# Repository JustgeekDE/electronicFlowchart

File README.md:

# electronicFlowchart
Electronic Flowchart - Physical flowchart components to create simple programs

Electronic Flowchart aims to make program flow charts more tangible. By connecting physical control nodes with actual wires and showing which node is active at any given time, the program flow is shown expölicitly while it's happening

## ToDos:
- Code

### Nodes
- Register node
- Conditional node
- indirect register selector (mux / load) node

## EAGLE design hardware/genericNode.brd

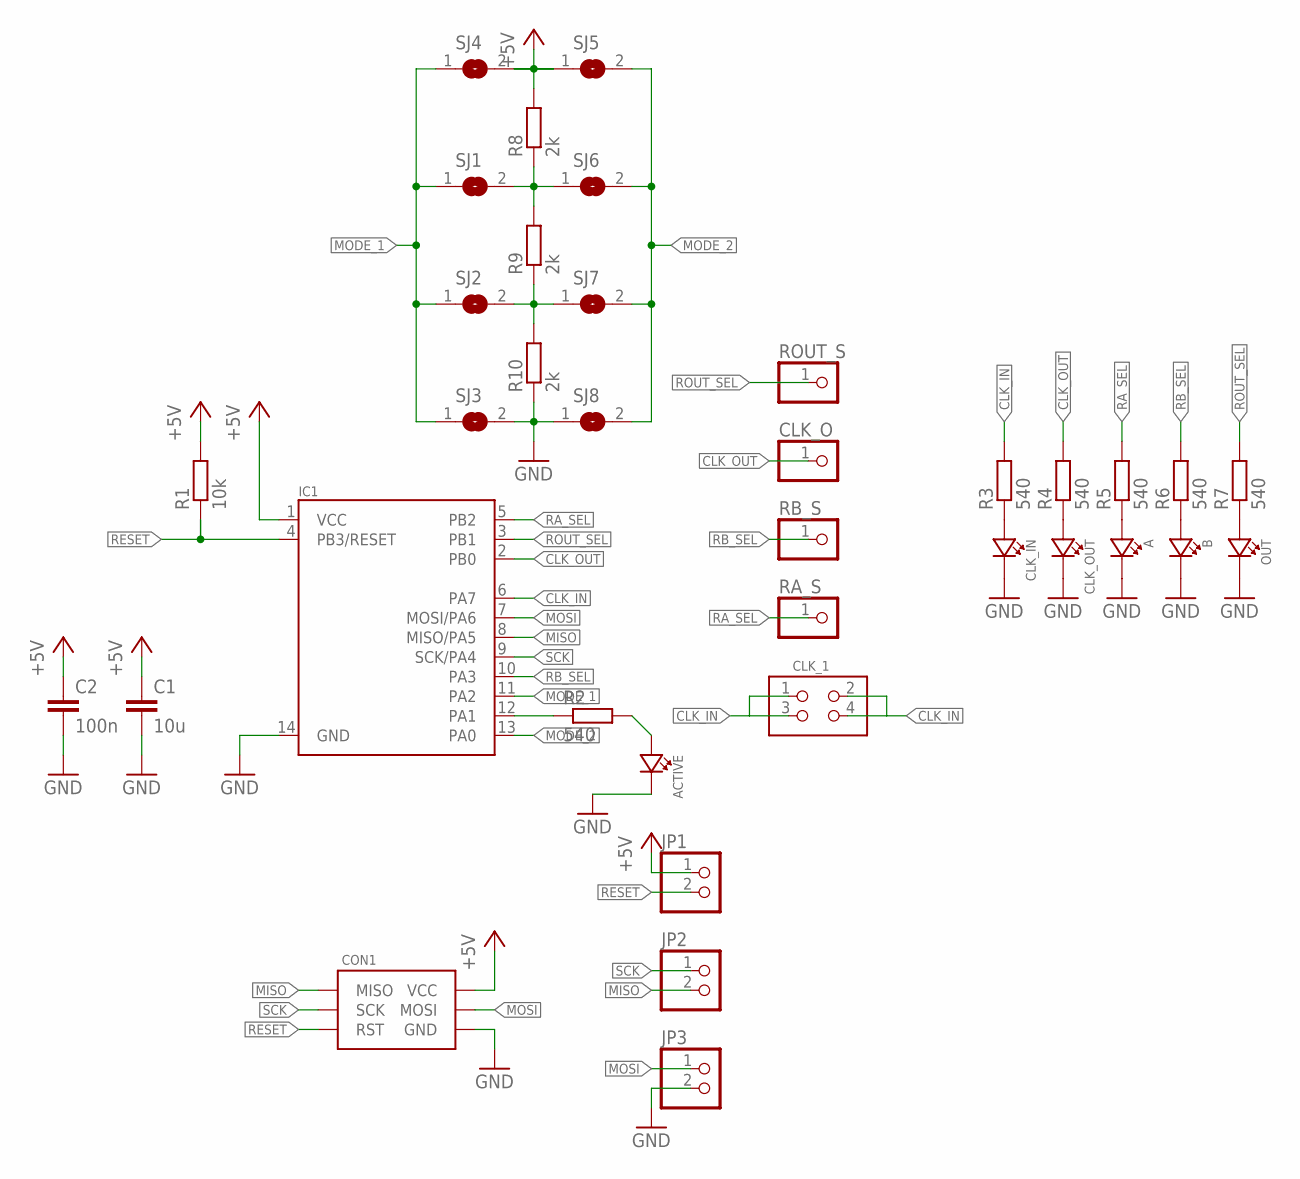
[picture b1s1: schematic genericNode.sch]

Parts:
A: LED0805; CHIPLED_0805
ACTIVE: LED0805; CHIPLED_0805
B: LED0805; CHIPLED_0805
C1: 10u; C0805
C2: 100n; C0603
CLK_1: GENERIC-2X2-EDGE; PINHEADER-100MIL-2X2-EDGE
CLK_IN: LED0805; CHIPLED_0805
CLK_O: PINHD-1X1; 1X01
CLK_OUT: LED0805; CHIPLED_0805
CON1: ISP-6_PIN-POGO; POGO-1.27-6_PIN-MADWORM
IC1: AVR-ATTINY24/44/84-SOIC14; SOIC14
JP1, JP2, JP3: PINHD-1X2; 1X02
OUT: LED0805; CHIPLED_0805
R1: 10k; R0603
R2, R3, R4, R5, R6, R7: 540; R0603
R8, R9, R10: 2k; R0603
RA_S: PINHD-1X1; 1X01
RB_S: PINHD-1X1; 1X01
ROUT_S: PINHD-1X1; 1X01
SJ1, SJ2, SJ3, SJ4, SJ5, SJ6, SJ7, SJ8: SJ

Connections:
+5V: C1.1, C2.1, CON1.P$2 (VCC), IC1.1 (VCC), JP1.1, R1.2, R8.2, SJ4.2, SJ5.1
CLK_IN: CLK_1.1, CLK_1.2, CLK_1.3, CLK_1.4, IC1.6 (PA7), R3.2
CLK_OUT: CLK_O.1, IC1.2 (PB0), R4.2
GND: A.C, ACTIVE.C, B.C, C1.2, C2.2, CLK_IN.C, CLK_OUT.C, CON1.P$6 (GND), IC1.14 (GND), JP3.2, OUT.C, R10.1, SJ3.2, SJ8.1
MISO: CON1.P$1 (MISO), IC1.8 (MISO/PA5), JP2.2
MODE_1: IC1.11 (PA2), SJ1.1, SJ2.1, SJ3.1, SJ4.1
MODE_2: IC1.13 (PA0), SJ5.2, SJ6.2, SJ7.2, SJ8.2
MOSI: CON1.P$4 (MOSI), IC1.7 (MOSI/PA6), JP3.1
unnamed: ACTIVE.A, R2.2
unnamed: IC1.12 (PA1), R2.1
unnamed: CLK_IN.A, R3.1
unnamed: CLK_OUT.A, R4.1
unnamed: A.A, R5.1
unnamed: B.A, R6.1
unnamed: R9.1, R10.2, SJ2.2, SJ7.1
unnamed: R8.1, R9.2, SJ1.2, SJ6.1
unnamed: OUT.A, R7.1
RA_SEL: IC1.5 (PB2), R5.2, RA_S.1
RB_SEL: IC1.10 (PA3), R6.2, RB_S.1
RESET: CON1.P$5 (RST), IC1.4 (PB3/RESET), JP1.2, R1.1
ROUT_SEL: IC1.3 (PB1), R7.2, ROUT_S.1
SCK: CON1.P$3 (SCK), IC1.9 (SCK/PA4), JP2.1

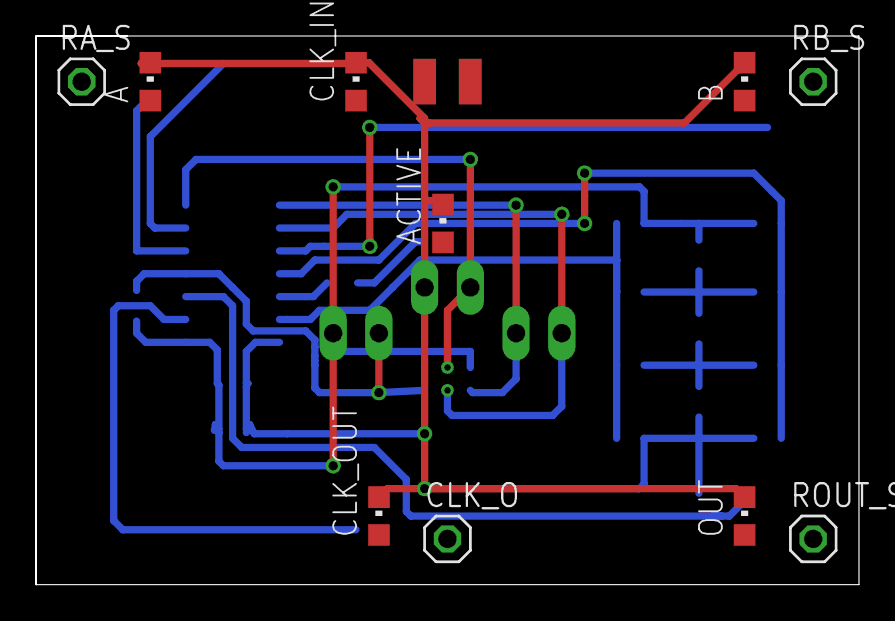
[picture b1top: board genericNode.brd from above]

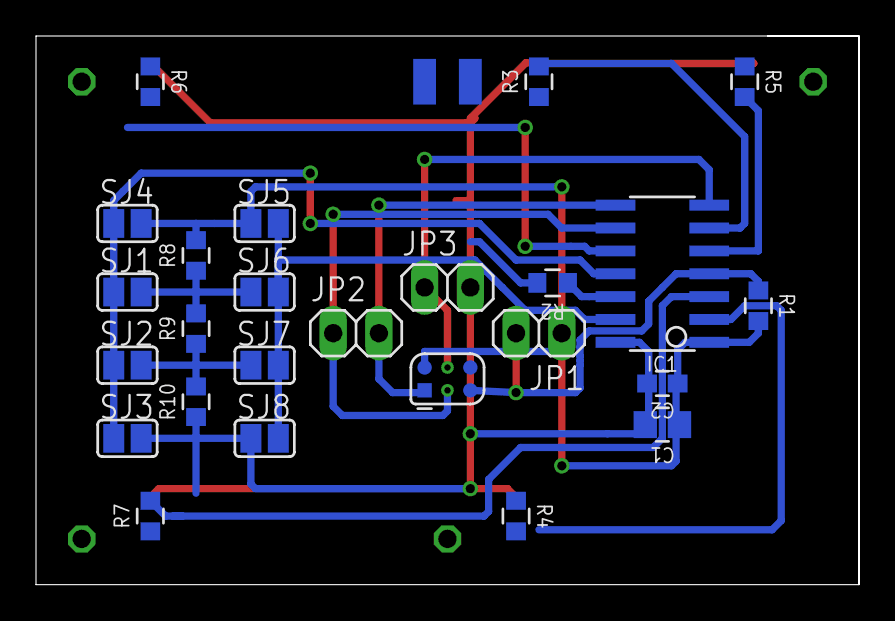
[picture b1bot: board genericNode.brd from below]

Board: 2 copper layers, 45.7 x 30.5 mm, 36 parts (25 on the bottom side), 22 nets.

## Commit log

2015-07-08 Initial checkin
2015-07-08 cleanup
